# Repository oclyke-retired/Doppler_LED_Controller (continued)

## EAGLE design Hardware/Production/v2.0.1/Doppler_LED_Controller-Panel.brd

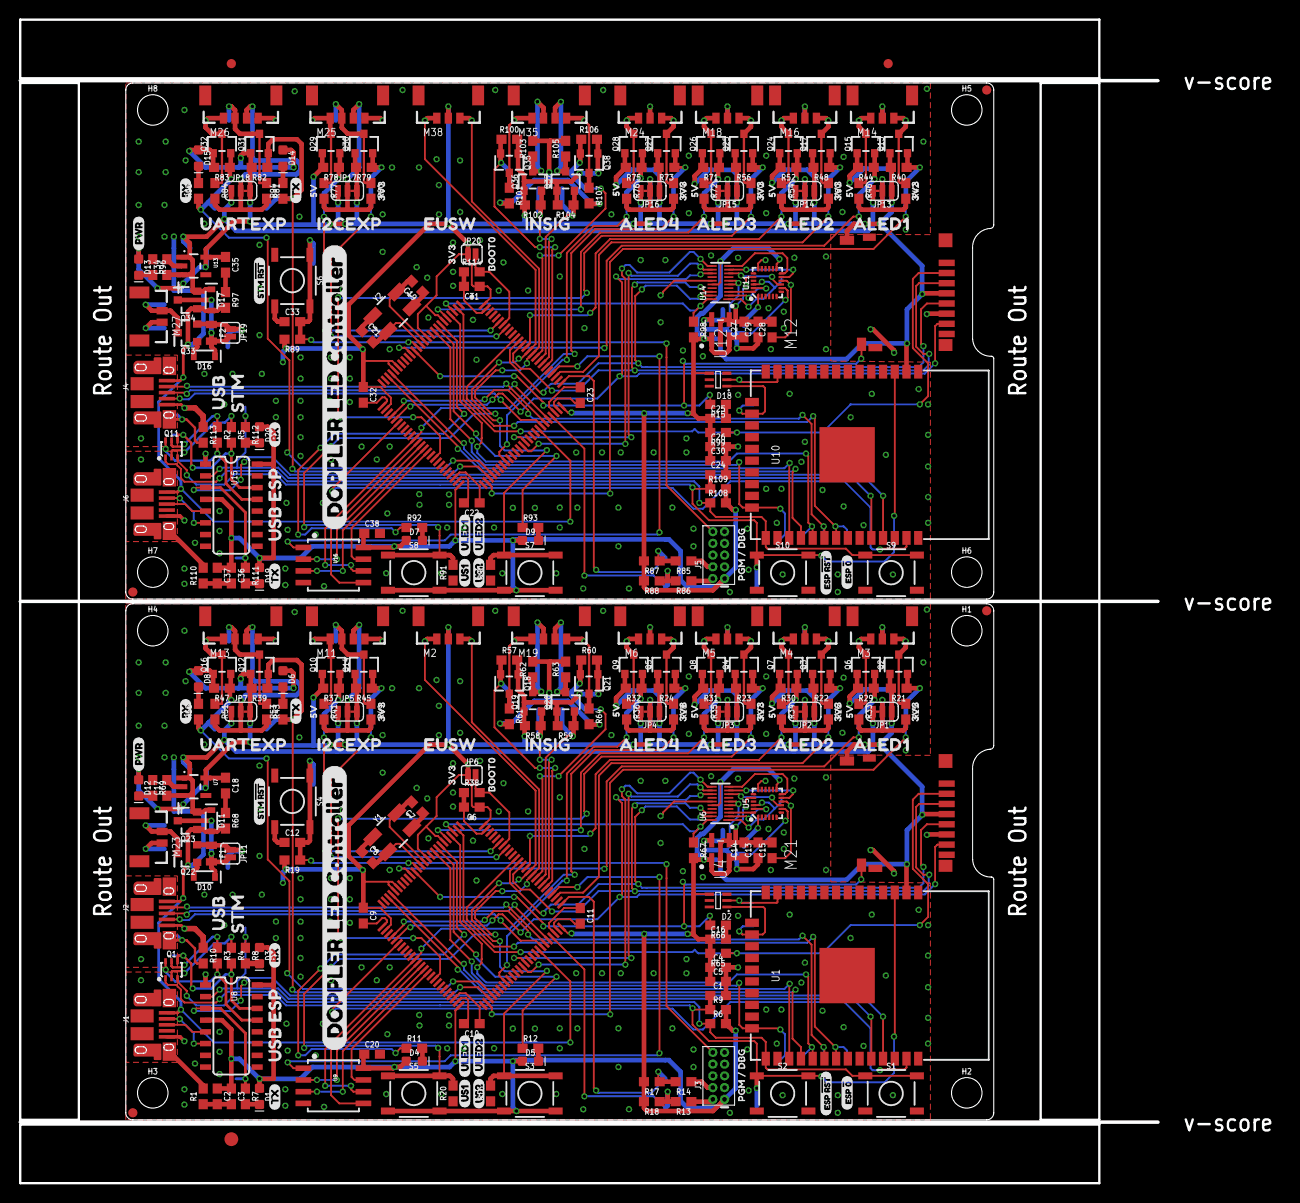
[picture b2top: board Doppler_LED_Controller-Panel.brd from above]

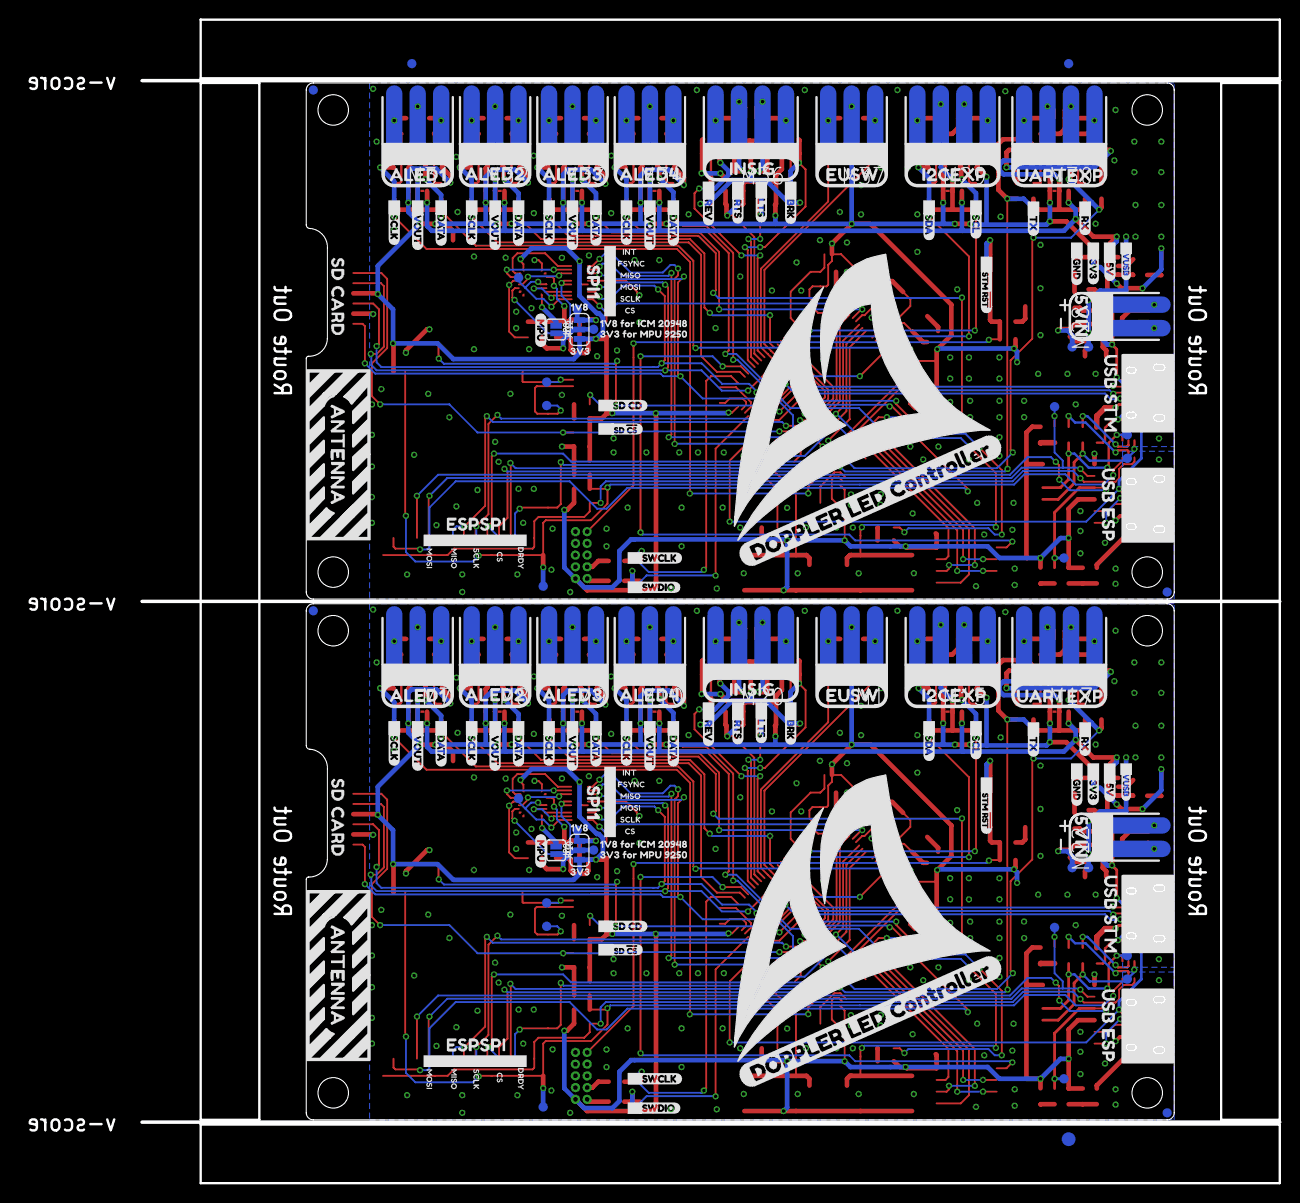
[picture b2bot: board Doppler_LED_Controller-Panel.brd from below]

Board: 2 copper layers, 123.2 x 126.0 mm, 628 parts (257 on the bottom side), 226 nets.

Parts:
C1, C3, C4, C6, C12, C13, C14, C15, C16, C20, C24, C25, C26, C27, C28, C29, C31, C33, C36, C38: 0.1uF; 0603
C2, C10, C11, C17, C18, C22, C23, C34, C35, C37: 2.2uF; 0603
C5, C9, C30, C32: 10uF; 0603
C7, C8, C19, C21: 18pF; 0603
D1, D19: ESPTX-GREEN; LED-0603
D2, D18: ESP_STAT; APA102_2020_LONG
D3, D20: ESPRX-YELLOW; LED-0603
D4, D7: ULED1-BLUE; LED-0603
D5, D9: ULED2-WHITE; LED-0603
D6, D14: U7TX-GREEN; LED-0603
D8, D15: U7RX-YELLOW; LED-0603
D10, D16: 5.6V; SOD-323
D11, D17: 3A/10V/280mV; SOD-323
D12, D13: PWR-RED; LED-0603
E$1, E$2, E$3, E$4: FIDUCIAL-1X2
E$5, E$6: FIDUCIAL-1.5X3
F1, F2: PPTC_6V500MA; 0805
FD1, FD2, FD3, FD4, FD5, FD6, FD7, FD8: FIDUCIAL1X2; FIDUCIAL-1X2
H1, H2, H3, H4, H5, H6, H7, H8: STAND-OFF
J1, J2, J4, J6: USB-MICROB-PTH-MILL
J3, J5: CORTEX_DEBUG_PTH; 2X5-PTH-1.27MM
JP1, JP13: ALED1_VOUT_SEL; SMT-JUMPER_3_1-NC_TRACE_SILK
JP2, JP14: ALED2_VOUT_SEL; SMT-JUMPER_3_1-NC_TRACE_SILK
JP3, JP15: ALED3_VOUT_SEL; SMT-JUMPER_3_1-NC_TRACE_SILK
JP4, JP16: ALED4_VOUT_SEL; SMT-JUMPER_3_1-NC_TRACE_SILK
JP5, JP7, JP17, JP18: I2C1_VOUT_SEL; SMT-JUMPER_3_1-NC_TRACE_SILK
JP6, JP20: JUMPER-SMT_2_NO_SILK; SMT-JUMPER_2_NO_SILK
JP8, JP9: IMU_VSEL; SMT-JUMPER_3_1-NC_TRACE_SILK
JP10, JP12: MPU9250; SMT-JUMPER_2_NO_SILK
JP11, JP19: DEFUSE; SMT-JUMPER_2_NO_SILK
M1, M37: EXT_SWTCH; 1X03_SMD_0.1IN
M2, M38: EXT_SWTCH; 3_PIN_LOCK
M3, M14: ALED1_LOCK; 3_PIN_LOCK
M4, M16: ALED2_LOCK; 3_PIN_LOCK
M5, M18: ALED3_LOCK; 3_PIN_LOCK
M6, M24: ALED4_LOCK; 3_PIN_LOCK
M7, M31: ALED1_SMD; 1X03_SMD_0.1IN
M8, M32: ALED2_SMD; 1X03_SMD_0.1IN
M9, M33: ALED3_SMD; 1X03_SMD_0.1IN
M10, M34: ALED4_SMD; 1X03_SMD_0.1IN
M11, M25: I2C1_LOCK; 4_PIN_LOCK
M12, M21: SD; SD_AMPHENOL_PUSH_PULL
M13, M26: U7_LOCK; 4_PIN_LOCK
M15, M29: I2C1_SMD; 1X04_SMD_0.1IN
M17, M30: U7_SMD; 1X04_SMD_0.1IN
M19, M35: SIG_IN_LOCK; 4_PIN_LOCK
M20, M36: SIG_IN_SMD; 1X04_SMD_0.1IN
M22, M28: 1X02_SMD_0.1IN
M23, M27: 2_PIN_LOCK
Q1, Q11: SC70-6
Q2, Q3, Q4, Q5, Q6, Q7, Q8, Q9, Q10, Q12, Q13, Q14, Q15, Q16, Q17, Q18, Q19, Q20, Q21, Q24, Q25, Q26, Q27, Q28, Q29, Q30, Q31, Q32, Q35, Q36, Q37, Q38: SOT23-3
Q22, Q23, Q33, Q34: 4.3A/20V/54mΩ; SOT23-3
R1, R10, R110, R113: DNP; 0603
R2, R3, R4, R5, R6, R9, R15, R16, R17, R18, R19, R20, R21, R22, R23, R24, R25, R26, R27, R28, R29, R30, R31, R32, R33, R34, R35, R36, R38, R39, R40, R42, R43, R44, R46, R47, R48, R50, R51, R52, R54, R56, R57, R58, R59, R60, R61, R62, R63, R64, R65, R66, R67, R68, R70, R71, R72, R73, R74, R75, R76, R81, R82, R83, R84, R87, R88, R89, R90, R91, R97, R98, R99, R100, R101, R102, R103, R104, R105, R106, R107, R108, R109, R114: 10k; 0603
R7, R8, R11, R12, R53, R55, R69, R92, R93, R94, R95, R96, R111, R112: 1k; 0603
R13, R14, R85, R86: 20; 0603
R37, R41, R45, R49, R77, R78, R79, R80: 2.2k; 0603
S1, S2, S3, S7, S9, S10: US2; TACTILE_SWITCH_SMD_5.2MM
S4, S6: STM_!RST; TACTILE_SWITCH_SMD_5.2MM
S5, S8: US1; TACTILE_SWITCH_SMD_5.2MM
TP1, TP104: EDRDY; PAD.03X.04
TP2, TP3: ERX0; PAD.03X.04
TP4, TP14: ETX0; PAD.03X.04
TP5, TP15: E!RTS; PAD.03X.04
TP6, TP16: E!DTR; PAD.03X.04
TP7, TP19: EMOSI; PAD.03X.04
TP8, TP26: EMISO; PAD.03X.04
TP9, TP27: ESCLK; PAD.03X.04
TP10, TP28: ECS; PAD.03X.04
TP11, TP32: ESSI; PAD.03X.04
TP12, TP33: ESSCK; PAD.03X.04
TP13, TP46: E!RST; PAD.03X.04
TP17, TP63: VDDIO; PAD.03X.04
TP18, TP73: 1V8; PAD.03X.04
TP20, TP55: S1Si; PAD.03X.04
TP21, TP56: S1SO; PAD.03X.04
TP22, TP59: S1SCLk; PAD.03X.04
TP23, TP60: CSSD; PAD.03X.04
TP24, TP61: CSIMU; PAD.03X.04
TP25, TP64: SDCD; PAD.03X.04
TP29, TP65: CSIMUIO; PAD.03X.04
TP30, TP66: IMUINT; PAD.03X.04
TP31, TP67: IMUFS; PAD.03X.04
TP34, TP81: AL1D; PAD.03X.04
TP35, TP84: AL2D; PAD.03X.04
TP36, TP87: AL3D; PAD.03X.04
TP37, TP90: AL4D; PAD.03X.04
TP38, TP82: AL1V; PAD.03X.04
TP39, TP85: AL2V; PAD.03X.04
TP40, TP88: AL3V; PAD.03X.04
TP41, TP91: AL4V; PAD.03X.04
TP42, TP83: AL1C; PAD.03X.04
TP43, TP86: AL2C; PAD.03X.04
TP44, TP89: AL3C; PAD.03X.04
TP45, TP92: AL4C; PAD.03X.04
TP47, TP74: VRPP; PAD.03X.04
TP48, TP75: VOVP; PAD.03X.04
TP49, TP76: VUSB; PAD.03X.04
TP50, TP77: 5V; PAD.03X.04
TP51, TP79: 3V3; PAD.03X.04
TP52, TP80: GND; PAD.03X.04
TP53, TP97: IIC1SDA; PAD.03X.04
TP54, TP98: IIC1SCL; PAD.03X.04
TP57, TP99: U7TX; PAD.03X.04
TP58, TP100: U7RX; PAD.03X.04
TP62, TP101: STMR; PAD.03X.04
TP68, TP102: SWCLK; PAD.03X.04
TP69, TP93: BRK; PAD.03X.04
TP70, TP94: LTS; PAD.03X.04
TP71, TP95: RTS; PAD.03X.04
TP72, TP96: REV; PAD.03X.04
TP78, TP103: SWDIO; PAD.03X.04
U1, U10: ESP-WROOM-32
U2, U3: LQFP-100
U4, U12: 1.8V; DDC5
U5, U11: 9DoF IMU; QFN24-3X3
U6, U14: TXB0108DQSR; UFDFN-20
U7, U13: 3.3V; SOT23-5
U8, U15: CH340C; SO016
U9, U16: W25Q32FVSS; SOIC-8
U$1, U$70, U$74, U$168: ALED10
U$2, U$75, U$101, U$169: ALED21
U$3, U$102: ALED43
U$4, U$76, U$103, U$170: ALED33
U$5, U$78, U$104, U$172: INSIG4
U$6, U$79, U$105, U$173: UARTEXP7
U$7, U$80, U$106, U$174: I2CEXP6
U$8, U$81, U$107, U$175: EUSW5
U$9, U$10, U$11, U$12, U$108, U$109, U$110, U$111: SCLK1
U$13, U$14, U$15, U$16, U$112, U$113, U$114, U$115: VOUT2
U$17, U$18, U$19, U$20, U$116, U$117, U$118, U$119: DATA0
U$21, U$120: RTS4
U$22, U$121: LTS3
U$23, U$122: BRK5
U$24, U$123: REV6
U$25, U$124: SCL8
U$26, U$125: SDA7
U$27, U$63, U$66, U$126, U$158, U$161: TX9
U$28, U$64, U$67, U$127, U$159, U$162: RX10
U$29, U$128: 5VIN8
U$30, U$186: VUSB15
U$31, U$187: 5V14
U$32, U$188: 3V313
U$33, U$189: GND12
U$34, U$129: SWCLK16
U$35, U$130: SWDIO15
U$36, U$48, U$131, U$143: SCLK20
U$37, U$49, U$132, U$144: CS21
U$38, U$47, U$133, U$142: MISO18
U$39, U$46, U$134, U$141: MOSI17
U$40, U$135: DRDY19
U$41, U$136: ESPSPI9
U$42, U$137: ANTENNA10
U$43, U$138: SD_CARD11
U$44, U$71, U$139, U$165: USB_ESP12
U$45, U$140: USB_STM13
U$50, U$145: FSYNC23
U$51, U$146: INT22
U$52, U$147: STM_#RST26
U$53, U$148: SD_#CS24
U$54, U$149: SD_CD27
U$55, U$68, U$150, U$163: DOPPLER_LED_CONTROLLER0
U$56, U$151: ULED23
U$57, U$152: ULED12
U$58, U$153: US10
U$59, U$154: US21
U$60, U$155: ESP_#RST5
U$61, U$156: ESP_#06
U$62, U$157: PGM_#_DBG7
U$65, U$160: PWR8
U$69, U$164: STM_#RST24
U$72, U$82, U$83, U$84, U$85, U$86, U$166, U$176, U$177, U$178, U$179, U$180: 3V310
U$73, U$167: BOOT09
U$77, U$171: ALED42
U$87, U$88, U$89, U$90, U$91, U$181, U$182, U$183, U$184, U$185: 5V11
U$92, U$190: SPI116
U$93, U$191: 3V39
U$94, U$192: 1V817
U$95, U$193: 1V8_FOR_ICM_2094818
U$96, U$194: 3V3_FOR_MPU_925019
U$97, U$195: MPU20
U$98, U$196: REV_NUM
U$99, U$197: USB0
U$100, U$198: STM1
Y1, Y2: 24MHz; CRYSTAL-SMD-5X3.2-4PAD

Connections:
1.8V: JP9.3, TP18.P$1, U4.5
1.8V1: JP8.3, TP73.P$1, U12.5
3.3V: C2.1, C3.1, C4.1, C5.1, C6.1, C9.1, C14.1, C16.1, C18.1, C20.1, D1.A, D2.4VCC, D3.A, D4.A, D5.A, D6.A, D8.A, D12.A, J3.1, JP1.1, JP2.1, JP3.1, JP4.1, JP5.3, JP6.1, JP7.3, JP9.1, M1.P$2, M2.P$2, M21.CD_SW2, M21.P$4, Q2.1, Q3.1, Q4.1, Q5.1, Q6.1, Q7.1, Q8.1, Q9.1, Q10.1, Q12.1, Q14.1, Q16.1, Q18.1, Q19.1, Q20.1, Q21.1, R6.2, R9.2, R17.2, R18.2, R19.2, R21.2, R22.2, R23.2, R24.2, R29.2, R30.2, R31.2, R32.2, R37.2, R39.2, R45.2, R47.2, R57.2, R58.2, R59.2, R60.2, R65.2, R67.2, S3.3, S3.4, S5.3, S5.4, TP51.P$1, U1.2, U3.P$6, U3.P$11, U3.P$20, U3.P$21, U3.P$27, U3.P$50, U3.P$75, U3.P$100, U4.1, U4.3, U5.13, U6.16, U7.5, U8.4, U8.16, U9.8
3.3V1: C25.1, C26.1, C27.1, C30.1, C31.1, C32.1, C35.1, C36.1, C37.1, C38.1, D7.A, D9.A, D13.A, D14.A, D15.A, D18.4VCC, D19.A, D20.A, J5.1, JP8.1, JP13.1, JP14.1, JP15.1, JP16.1, JP17.3, JP18.3, JP20.1, M12.CD_SW2, M12.P$4, M37.P$2, M38.P$2, Q13.1, Q15.1, Q17.1, Q24.1, Q25.1, Q26.1, Q27.1, Q28.1, Q29.1, Q30.1, Q31.1, Q32.1, Q35.1, Q36.1, Q37.1, Q38.1, R40.2, R44.2, R48.2, R52.2, R56.2, R71.2, R73.2, R75.2, R78.2, R79.2, R82.2, R83.2, R87.2, R88.2, R89.2, R98.2, R99.2, R100.2, R102.2, R104.2, R106.2, R108.2, R109.2, S7.3, S7.4, S8.3, S8.4, TP79.P$1, U2.P$6, U2.P$11, U2.P$20, U2.P$21, U2.P$27, U2.P$50, U2.P$75, U2.P$100, U10.2, U11.13, U12.1, U12.3, U13.5, U14.16, U15.4, U15.16, U16.8
5V: C17.1, D11.C, JP1.3, JP2.3, JP3.3, JP4.3, JP5.1, JP7.1, Q23.2, TP50.P$1, U7.1, U7.3
5V1: C34.1, D17.C, JP13.3, JP14.3, JP15.3, JP16.3, JP17.1, JP18.1, Q34.2, TP77.P$1, U13.1, U13.3
ALED1_MOSI_VOUT: M3.P$1, M7.P$1, Q6.3, R33.1
ALED1_MOSI_VOUT1: M14.P$1, M31.P$1, Q15.3, R46.1
ALED1_SCLK_VOUT: M3.P$3, M7.P$3, Q2.3, R25.1
ALED1_SCLK_VOUT1: M14.P$3, M31.P$3, Q13.3, R42.1
ALED1_VOUT: JP1.2, R25.2, R33.2, TP38.P$1
ALED1_VOUT1: JP13.2, R42.2, R46.2, TP82.P$1
ALED2_MOSI_VOUT: M4.P$1, M8.P$1, Q7.3, R34.1
ALED2_MOSI_VOUT1: M16.P$1, M32.P$1, Q24.3, R54.1
ALED2_SCLK_VOUT: M4.P$3, M8.P$3, Q3.3, R26.1
ALED2_SCLK_VOUT1: M16.P$3, M32.P$3, Q17.3, R50.1
ALED2_VOUT: JP2.2, R26.2, R34.2, TP39.P$1
ALED2_VOUT1: JP14.2, R50.2, R54.2, TP85.P$1
ALED3_MOSI_VOUT: M5.P$1, M9.P$1, Q8.3, R35.1
ALED3_MOSI_VOUT1: M18.P$1, M33.P$1, Q26.3, R72.1
ALED3_SCLK_VOUT: M5.P$3, M9.P$3, Q4.3, R27.1
ALED3_SCLK_VOUT1: M18.P$3, M33.P$3, Q25.3, R70.1
ALED3_VOUT: JP3.2, R27.2, R35.2, TP40.P$1
ALED3_VOUT1: JP15.2, R70.2, R72.2, TP88.P$1
ALED4_MOSI_VOUT: M6.P$1, M10.P$1, Q9.3, R36.1
ALED4_MOSI_VOUT1: M24.P$1, M34.P$1, Q28.3, R76.1
ALED4_SCLK_VOUT: M6.P$3, M10.P$3, Q5.3, R28.1
ALED4_SCLK_VOUT1: M24.P$3, M34.P$3, Q27.3, R74.1
ALED4_VOUT: JP4.2, R28.2, R36.2, TP41.P$1
ALED4_VOUT1: JP16.2, R74.2, R76.2, TP91.P$1
BOOT0: JP6.2, R38.2, U3.P$94
BOOT1: JP20.2, R114.2, U2.P$94
BRK: Q18.2, R57.1, TP69.P$1, U3.P$81
BRK1: Q35.2, R100.1, TP93.P$1, U2.P$81
BRK_12V: M19.P$1, M20.P$1, Q18.3, R61.1
BRK_12V1: M35.P$1, M36.P$1, Q35.3, R101.1
CS_ESP: TP10.P$1, U1.29, U3.P$4
CS_ESP1: TP28.P$1, U2.P$4, U10.29
CS_IMU: R67.1, TP24.P$1, U3.P$3, U6.20
CS_IMU1: R98.1, TP61.P$1, U2.P$3, U14.20
CS_IMU_VDDIO: TP29.P$1, U5.22, U6.1
CS_IMU_VDDIO1: TP65.P$1, U11.22, U14.1
CS_SD: M21.P$2, R65.1, TP23.P$1, U3.P$2
CS_SD1: M12.P$2, R99.1, TP60.P$1, U2.P$2
ESP_0: Q1.1, R6.1, S1.1, S1.2, U1.25
ESP_1: Q11.1, R108.1, S9.1, S9.2, U10.25
ESP_!DTR: Q1.6, R3.2, TP6.P$1, U8.13
ESP_!DTR1: Q11.6, R2.2, TP16.P$1, U15.13
ESP_!RESET: C1.1, Q1.3, R9.1, S2.1, S2.2, TP13.P$1, U1.3
ESP_!RESET1: C24.1, Q11.3, R109.1, S10.1, S10.2, TP46.P$1, U10.3
ESP_!RTS: Q1.4, R4.2, TP5.P$1, U8.14
ESP_!RTS1: Q11.4, R5.2, TP15.P$1, U15.14
ESP_DRDY: TP1.P$1, U1.24, U3.P$9
ESP_DRDY1: TP104.P$1, U2.P$9, U10.24
ESP_RXI0: R8.1, TP3.P$1, U1.34, U8.2
ESP_RXI1: R112.1, TP2.P$1, U10.34, U15.2
ESP_STAT_MOSI: D2.1DIN, TP11.P$1, U1.16
ESP_STAT_MOSI1: D18.1DIN, TP32.P$1, U10.16
ESP_STAT_SCLK: D2.2CIN, TP12.P$1, U1.13
ESP_STAT_SCLK1: D18.2CIN, TP33.P$1, U10.13
ESP_TXO0: R7.1, TP4.P$1, U1.35, U8.3
ESP_TXO1: R111.1, TP14.P$1, U10.35, U15.3
ESP_USB_DM: J1.D-, U8.6
ESP_USB_DM1: J6.D-, U15.6
ESP_USB_DP: J1.D+, U8.5
ESP_USB_DP1: J6.D+, U15.5
GND: C1.2, C2.2, C3.2, C4.2, C5.2, C6.2, C7.1, C8.1, C9.2, C10.2, C11.2, C12.1, C13.2, C14.2, C15.2, C16.2, C17.2, C18.2, C20.2, D2.3GND, D10.A, J1.GND, J2.GND, J3.3, J3.5, J3.9, M3.P$2, M4.P$2, M5.P$2, M6.P$2, M7.P$2, M8.P$2, M9.P$2, M10.P$2, M11.P$4, M13.P$4, M15.P$4, M17.P$4, M21.P$6, M22.P$1, M23.P$2, Q22.1, R1.1, R10.1, R16.1, R20.1, R38.1, R61.2, R62.2, R63.2, R64.2, R66.1, R68.1, R69.1, S1.3, S1.4, S2.3, S2.4, S4.3, S4.4, TP52.P$1, U1.1, U1.15, U1.38, U1.GND, U3.P$10, U3.P$19, U3.P$26, U3.P$49, U3.P$74, U3.P$99, U4.2, U4.4, U5.18, U5.20, U6.15, U7.2, U8.1, U9.4, Y1.2, Y1.4
GND1: C19.1, C21.1, C22.2, C23.2, C24.2, C25.2, C26.2, C27.2, C28.2, C29.2, C30.2, C31.2, C32.2, C33.1, C34.2, C35.2, C36.2, C37.2, C38.2, D16.A, D18.3GND, J4.GND, J5.3, J5.5, J5.9, J6.GND, M12.P$6, M14.P$2, M16.P$2, M18.P$2, M24.P$2, M25.P$4, M26.P$4, M27.P$2, M28.P$1, M29.P$4, M30.P$4, M31.P$2, M32.P$2, M33.P$2, M34.P$2, Q33.1, R15.1, R90.1, R91.1, R96.1, R97.1, R101.2, R103.2, R105.2, R107.2, R110.1, R113.1, R114.1, S6.3, S6.4, S9.3, S9.4, S10.3, S10.4, TP80.P$1, U2.P$10, U2.P$19, U2.P$26, U2.P$49, U2.P$74, U2.P$99, U10.1, U10.15, U10.38, U10.GND, U11.18, U11.20, U12.2, U12.4, U13.2, U14.15, U15.1, U16.4, Y2.2, Y2.4
I2C1_SCL: Q10.2, R37.1, TP54.P$1, U3.P$95
I2C1_SCL1: Q29.2, R78.1, TP98.P$1, U2.P$95
I2C1_SCL_VOUT: M11.P$1, M15.P$1, Q10.3, R41.1
I2C1_SCL_VOUT1: M25.P$1, M29.P$1, Q29.3, R77.1
I2C1_SDA: Q14.2, R45.1, TP53.P$1, U3.P$93
I2C1_SDA1: Q30.2, R79.1, TP97.P$1, U2.P$93
I2C1_SDA_VOUT: M11.P$2, M15.P$2, Q14.3, R49.1
I2C1_SDA_VOUT1: M25.P$2, M29.P$2, Q30.3, R80.1
I2C1_VOUT: JP5.2, M11.P$3, M15.P$3, R41.2, R49.2
I2C1_VOUT1: JP17.2, M25.P$3, M29.P$3, R77.2, R80.2
IMU_FSYNC: TP31.P$1, U3.P$64, U6.12
IMU_FSYNC1: TP67.P$1, U2.P$64, U14.12
IMU_FSYNC_VDDIO: U5.11, U6.9
IMU_FSYNC_VDDIO1: U11.11, U14.9
IMU_INT: TP30.P$1, U3.P$63, U6.11
IMU_INT1: TP66.P$1, U2.P$63, U14.11
IMU_INT_VDDIO: U5.12, U6.10
IMU_INT_VDDIO1: U11.12, U14.10
IMU_RESV1: JP10.1, U5.1
IMU_RESV2: JP12.1, U11.1
IMU_VDDIO: C13.1, JP9.2, JP10.2, TP17.P$1, U5.8, U6.5, U6.6
IMU_VDDIO1: C29.1, JP8.2, JP12.2, TP63.P$1, U11.8, U14.5, U14.6
LTS: Q19.2, R58.1, TP70.P$1, U3.P$82
LTS1: Q36.2, R102.1, TP94.P$1, U2.P$82
LTS_12V: M19.P$2, M20.P$2, Q19.3, R62.1
LTS_12V1: M35.P$2, M36.P$2, Q36.3, R103.1
unnamed: C23.1, U2.P$73
unnamed: J2.SHIELD, J2.SHIELD2, J2.SHIELD3, J2.SHIELD4, J2.SHIELD5, J2.SHIELD6, J2.SHIELD7, J2.SHIELD8, J2.SHIELD9, J2.SHIELD10, R10.2
unnamed: C11.1, U3.P$73
unnamed: J1.SHIELD, J1.SHIELD2, J1.SHIELD3, J1.SHIELD4, J1.SHIELD5, J1.SHIELD6, J1.SHIELD7, J1.SHIELD8, J1.SHIELD9, J1.SHIELD10, R1.2
unnamed: C10.1, U3.P$48
unnamed: C22.1, U2.P$48
unnamed: Q1.5, R3.1
unnamed: Q1.2, R4.1
unnamed: Q11.5, R2.1
unnamed: Q11.2, R5.1
unnamed: C28.1, U11.10
unnamed: J5.2, R86.1
unnamed: C15.1, U5.10
unnamed: J5.4, R85.1
unnamed: D8.C, R55.2
unnamed: J3.2, R13.1
unnamed: J3.4, R14.1
unnamed: D15.C, R95.2
unnamed: D6.C, R53.2
unnamed: D1.C, R7.2
unnamed: D3.C, R8.2
unnamed: D12.C, R69.2
unnamed: D14.C, R94.2
unnamed: D13.C, R96.2
unnamed: D5.C, R12.2
unnamed: D4.C, R11.2
unnamed: D9.C, R93.2
unnamed: D7.C, R92.2
unnamed: J6.SHIELD, J6.SHIELD2, J6.SHIELD3, J6.SHIELD4, J6.SHIELD5, J6.SHIELD6, J6.SHIELD7, J6.SHIELD8, J6.SHIELD9, J6.SHIELD10, R110.2
unnamed: D19.C, R111.2
unnamed: D20.C, R112.2
unnamed: J4.SHIELD, J4.SHIELD2, J4.SHIELD3, J4.SHIELD4, J4.SHIELD5, J4.SHIELD6, J4.SHIELD7, J4.SHIELD8, J4.SHIELD9, J4.SHIELD10, R113.2
PH0: C7.2, U3.P$12, Y1.3
PH1: C8.2, U3.P$13, Y1.1
PH2: C21.2, U2.P$13, Y2.1
PH3: C19.2, U2.P$12, Y2.3
QSPI_BK1_IO0: Q9.2, R32.1, TP37.P$1, U3.P$58
QSPI_BK1_IO5: Q28.2, R75.1, TP90.P$1, U2.P$58
QSPI_BK2_IO0: U3.P$37, U9.5
QSPI_BK2_IO1: U3.P$38, U9.2
QSPI_BK2_IO2: U3.P$39, U9.3
QSPI_BK2_IO3: U3.P$40, U9.7
QSPI_BK2_IO4: U2.P$37, U16.5
QSPI_BK2_IO5: U2.P$38, U16.2
QSPI_BK2_IO6: U2.P$39, U16.3
QSPI_BK2_IO7: U2.P$40, U16.7
QSPI_BK2_NCS: U3.P$79, U9.1
QSPI_BK2_NCS1: U2.P$79, U16.1
QSPI_SCLK: Q5.2, R24.1, TP45.P$1, U3.P$36, U9.6
QSPI_SCLK1: Q27.2, R73.1, TP92.P$1, U2.P$36, U16.6
REV: Q21.2, R60.1, TP72.P$1, U3.P$84
REV1: Q38.2, R106.1, TP96.P$1, U2.P$84
REV_12V: M19.P$4, M20.P$4, Q21.3, R64.1
REV_12V1: M35.P$4, M36.P$4, Q38.3, R107.1
RTS: Q20.2, R59.1, TP71.P$1, U3.P$83
RTS1: Q37.2, R104.1, TP95.P$1, U2.P$83
RTS_12V: M19.P$3, M20.P$3, Q20.3, R63.1
RTS_12V1: M35.P$3, M36.P$3, Q37.3, R105.1
SD_CD: M21.CD_SW1, R66.2, TP25.P$1, U3.P$15
SD_CD1: M12.CD_SW1, R15.2, TP64.P$1, U2.P$15
SPI1_MISO: M21.P$7, TP21.P$1, U3.P$30, U6.13
SPI1_MISO1: M12.P$7, TP56.P$1, U2.P$30, U14.13
SPI1_MISO_VDDIO: U5.9, U6.8
SPI1_MISO_VDDIO1: U11.9, U14.8
SPI1_MOSI: M21.P$3, TP20.P$1, U3.P$88, U6.18
SPI1_MOSI1: M12.P$3, TP55.P$1, U2.P$88, U14.18
SPI1_MOSI_VDDIO: U5.24, U6.3
SPI1_MOSI_VDDIO1: U11.24, U14.3
SPI1_SCLK: M21.P$5, TP22.P$1, U3.P$89, U6.19
SPI1_SCLK1: M12.P$5, TP59.P$1, U2.P$89, U14.19
SPI1_SCLK_VDDIO: U5.23, U6.2
SPI1_SCLK_VDDIO1: U11.23, U14.2
SPI2_MOSI: Q6.2, R29.1, TP34.P$1, U3.P$16
SPI2_MOSI1: Q15.2, R44.1, TP81.P$1, U2.P$16
SPI2_SCLK: Q2.2, R21.1, TP42.P$1, U3.P$52
SPI2_SCLK1: Q13.2, R40.1, TP83.P$1, U2.P$52
SPI3_MOSI: Q7.2, R30.1, TP35.P$1, U3.P$87
SPI3_MOSI1: Q24.2, R52.1, TP84.P$1, U2.P$87
SPI3_SCLK: Q3.2, R22.1, TP43.P$1, U3.P$78
SPI3_SCLK1: Q17.2, R48.1, TP86.P$1, U2.P$78
SPI4_MOSI: Q8.2, R31.1, TP36.P$1, U3.P$5
SPI4_MOSI1: Q26.2, R71.1, TP87.P$1, U2.P$5
SPI4_SCLK: Q4.2, R23.1, TP44.P$1, U3.P$42
SPI4_SCLK1: Q25.2, R56.1, TP89.P$1, U2.P$42
SPI6_MISO: TP8.P$1, U1.31, U3.P$90
SPI6_MISO1: TP26.P$1, U2.P$90, U10.31
SPI6_MOSI: TP7.P$1, U1.37, U3.P$31
SPI6_MOSI1: TP19.P$1, U2.P$31, U10.37
SPI6_SCLK: TP9.P$1, U1.30, U3.P$29
SPI6_SCLK1: TP27.P$1, U2.P$29, U10.30
STM_!RESET: C12.2, J3.10, R19.1, S4.1, S4.2, TP62.P$1, U3.P$14
STM_!RESET1: C33.2, J5.10, R89.1, S6.1, S6.2, TP101.P$1, U2.P$14
STM_USB_DM: J2.D-, U3.P$70
STM_USB_DM1: J4.D-, U2.P$70
STM_USB_DP: J2.D+, U3.P$71
STM_USB_DP1: J4.D+, U2.P$71
SWCLK: R14.2, R17.1, TP68.P$1, U3.P$76
SWCLK1: R85.2, R87.1, TP102.P$1, U2.P$76
SWDIO: R13.2, R18.1, TP78.P$1, U3.P$72
SWDIO1: R86.2, R88.1, TP103.P$1, U2.P$72
UART4_RX: U1.28, U3.P$23
UART4_RX1: U2.P$23, U10.28
UART4_TX: U1.27, U3.P$22
UART4_TX1: U2.P$22, U10.27
ULED1: R11.1, U3.P$7
ULED2: R12.1, U3.P$8
ULED3: R93.1, U2.P$8
ULED4: R92.1, U2.P$7
US1: M1.P$3, M2.P$3, R20.2, S5.1, S5.2, U3.P$85
US2: M1.P$1, M2.P$1, R16.2, S3.1, S3.2, U3.P$86
US3: M37.P$1, M38.P$1, R90.2, S7.1, S7.2, U2.P$86
US4: M37.P$3, M38.P$3, R91.2, S8.1, S8.2, U2.P$85
USART1_RX: Q16.2, R47.1, R55.1, TP58.P$1, U3.P$54
USART1_RX1: Q32.2, R83.1, R95.1, TP100.P$1, U2.P$54
USART1_RX_VOUT: M13.P$1, M17.P$1, Q16.3, R51.1
USART1_RX_VOUT1: M26.P$1, M30.P$1, Q32.3, R84.1
USART1_TX: Q12.2, R39.1, R53.1, TP57.P$1, U3.P$53
USART1_TX1: Q31.2, R82.1, R94.1, TP99.P$1, U2.P$53
USART1_TX_VOUT: M13.P$2, M17.P$2, Q12.3, R43.1
USART1_TX_VOUT1: M26.P$2, M30.P$2, Q31.3, R81.1
USART1_VOUT: JP7.2, M13.P$3, M17.P$3, R43.2, R51.2
USART1_VOUT1: JP18.2, M26.P$3, M30.P$3, R81.2, R84.2
USB_OTG_FS_ID: J2.ID, U3.P$69
USB_OTG_FS_ID1: J4.ID, U2.P$69
VOVP: D10.C, F1.2, JP11.2, Q23.3, TP48.P$1
VOVP1: D16.C, F2.2, JP19.2, Q34.3, TP75.P$1
VRAW: M22.P$2, M23.P$3, Q22.3
VRAW1: M27.P$3, M28.P$2, Q33.3
VRPP: F1.1, JP11.1, Q22.2, TP47.P$1
VRPP1: F2.1, JP19.1, Q33.2, TP74.P$1
V_USB: D11.A, J1.VBUS, J2.VBUS, Q23.1, R68.2, TP49.P$1, U3.P$68
V_USB1: D17.A, J4.VBUS, J6.VBUS, Q34.1, R97.2, TP76.P$1, U2.P$68

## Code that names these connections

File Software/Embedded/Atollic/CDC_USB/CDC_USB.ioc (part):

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Mcu.Name=STM32F765V(G-I)Tx
Mcu.Package=LQFP100
Mcu.UserName=STM32F765VGTx
PA0/WKUP.Mode=Asynchronous
PA0/WKUP.Signal=UART4_TX
PA1.Mode=Asynchronous
PA1.Signal=UART4_RX
PA11.Mode=Device_Only
PA11.Signal=USB_OTG_FS_DM
PA12.Mode=Device_Only
PA12.Signal=USB_OTG_FS_DP
PA13.Mode=Serial_Wire
PA13.Signal=SYS_JTMS-SWDIO
PA14.Mode=Serial_Wire
PA14.Signal=SYS_JTCK-SWCLK
PA5.Mode=Full_Duplex_Master
PA5.Signal=SPI6_SCK
PA6.Mode=Full_Duplex_Master
PA6.Signal=SPI1_MISO
PA7.Mode=Full_Duplex_Master
PA7.Signal=SPI6_MOSI
PA8.Mode=Activate_SOF_FS
PA8.Signal=USB_OTG_FS_SOF
PA9.Mode=Activate_VBUS
PA9.Signal=USB_OTG_FS_VBUS
PB10.Mode=I2C
PB10.Signal=I2C2_SCL
PB11.Mode=I2C
PB11.Signal=I2C2_SDA
PB12.Mode=Asynchronous
PB12.Signal=UART5_RX
PB13.Mode=TX_Only_Simplex_Unidirect_Master
PB13.Signal=SPI2_SCK
PB14.Mode=Asynchronous
PB14.Signal=USART1_TX
PB15.Mode=Asynchronous
PB15.Signal=USART1_RX
PB2.Mode=Dual Bank
PB2.Signal=QUADSPI_CLK
PB3.Mode=Full_Duplex_Master
PB3.Signal=SPI1_SCK
PB4.Mode=Full_Duplex_Master
PB4.Signal=SPI6_MISO
PB6.Mode=Enable Chip Select for each bank
PB6.Signal=QUADSPI_BK1_NCS
PB7.Mode=I2C
PB7.Signal=I2C1_SDA
PB8.Mode=I2C
PB8.Signal=I2C1_SCL
PC0.GPIOParameters=GPIO_Label
PC0.GPIO_Label=SD_CD
PC0.Signal=GPIO_Input
PC1.Mode=TX_Only_Simplex_Unidirect_Master
PC1.Signal=SPI2_MOSI
PC10.Mode=TX_Only_Simplex_Unidirect_Master
PC10.Signal=SPI3_SCK
PC11.Mode=Enable Chip Select for each bank
PC11.Signal=QUADSPI_BK2_NCS
PC12.Mode=Asynchronous
PC12.Signal=UART5_TX
PC13.GPIOParameters=PinState,GPIO_Label
PC13.GPIO_Label=ULED1
PC13.PinState=GPIO_PIN_SET
PC13.Signal=GPIO_Output
PC14/OSC32_IN.GPIOParameters=PinState,GPIO_PuPd,GPIO_Label
PC14/OSC32_IN.GPIO_Label=ULED2
PC14/OSC32_IN.GPIO_PuPd=GPIO_NOPULL
PC14/OSC32_IN.PinState=GPIO_PIN_SET
PC14/OSC32_IN.Signal=GPIO_Output
PC15/OSC32_OUT.GPIOParameters=GPIO_Label
PC15/OSC32_OUT.GPIO_Label=ESP_DRDY
PC15/OSC32_OUT.Signal=GPIO_Input
PC6.GPIOParameters=GPIO_Label
PC6.GPIO_Label=IMU_INT
PC6.Signal=GPIO_Input
PC7.GPIOParameters=GPIO_Label
PC7.GPIO_Label=IMU_FSYNC
PC7.Signal=GPIO_Input
PD0.GPIOParameters=GPIO_Label
PD0.GPIO_Label=BRK
PD0.Signal=GPIO_Input
PD1.GPIOParameters=GPIO_Label
PD1.GPIO_Label=LTS
PD1.Signal=GPIO_Input
PD11.Mode=Dual Bank
PD11.Signal=QUADSPI_BK1_IO0
PD12.Mode=Dual Bank
PD12.Signal=QUADSPI_BK1_IO1
PD13.Mode=Dual Bank
PD13.Signal=QUADSPI_BK1_IO3
PD2.GPIOParameters=GPIO_Label
PD2.GPIO_Label=RTS
PD2.Signal=GPIO_Input
PD3.GPIOParameters=GPIO_Label
PD3.GPIO_Label=REV
PD3.Signal=GPIO_Input
PD4.GPIOParameters=GPIO_Label
PD4.GPIO_Label=US1
PD4.Signal=GPIO_Input
PD5.GPIOParameters=GPIO_Label
PD5.GPIO_Label=US2
PD5.Signal=GPIO_Input
PD6.Mode=TX_Only_Simplex_Unidirect_Master
PD6.Signal=SPI3_MOSI
PD7.Mode=Full_Duplex_Master
PD7.Signal=SPI1_MOSI
PE0.Mode=Asynchronous
PE0.Signal=UART8_RX
PE1.Mode=Asynchronous
PE1.Signal=UART8_TX
PE10.Mode=Dual Bank
PE10.Signal=QUADSPI_BK2_IO3
PE12.Mode=TX_Only_Simplex_Unidirect_Master
PE12.Signal=SPI4_SCK
PE2.Mode=Dual Bank
PE2.Signal=QUADSPI_BK1_IO2
PE3.GPIOParameters=GPIO_Speed,PinState,GPIO_Label
PE3.GPIO_Label=CS_SD
PE3.GPIO_Speed=GPIO_SPEED_FREQ_VERY_HIGH
PE3.PinState=GPIO_PIN_SET
PE3.Signal=GPIO_Output
PE4.GPIOParameters=GPIO_Speed,PinState,GPIO_PuPd,GPIO_Label
PE4.GPIO_Label=CS_IMU
PE4.GPIO_PuPd=GPIO_NOPULL
PE4.GPIO_Speed=GPIO_SPEED_FREQ_VERY_HIGH
PE4.PinState=GPIO_PIN_SET
PE4.Signal=GPIO_Output
PE5.GPIOParameters=GPIO_Speed,PinState,GPIO_PuPd,GPIO_Label
PE5.GPIO_Label=CS_ESP
PE5.GPIO_PuPd=GPIO_NOPULL
PE5.GPIO_Speed=GPIO_SPEED_FREQ_VERY_HIGH
PE5.PinState=GPIO_PIN_SET
PE5.Signal=GPIO_Output
PE6.Mode=TX_Only_Simplex_Unidirect_Master
PE6.Signal=SPI4_MOSI
PE7.Mode=Dual Bank
PE7.Signal=QUADSPI_BK2_IO0
PE8.Mode=Dual Bank
PE8.Signal=QUADSPI_BK2_IO1
PE9.Mode=Dual Bank
PE9.Signal=QUADSPI_BK2_IO2
PH0/OSC_IN.Mode=HSE-External-Oscillator
PH0/OSC_IN.Signal=RCC_OSC_IN
PH1/OSC_OUT.Mode=HSE-External-Oscillator
PH1/OSC_OUT.Signal=RCC_OSC_OUT
RCC.HSE_VALUE=24000000
RCC.SYSCLKFreq_VALUE=216000000
RCC.SYSCLKSource=RCC_SYSCLKSOURCE_PLLCLK
board=custom

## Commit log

2018-11-28 Initial Commit
    In this commit all relevant files from the MT/AES project were copied into this repo.
2018-12-01 Added more resources
2018-12-01 Fixed clock and NVIC in default peripheral configuration
2018-12-16 Add SPI Flash Library and STM32F7 Quadspi port
2018-12-16 Add STM32F7 port for SPIDS
2018-12-16 Add SPIDS library
2018-12-16 Add SPIDS supporting files
2018-12-16 Add USB specification documents
2018-12-16 Add USB Device Configuration
2018-12-16 Add USB CDC example project
2018-12-16 Add DoppBoot project
2018-12-16 Add ESP Relay project
2018-12-16 Add USB MSC example project
2018-12-24 Add print header
2018-12-24 Add doppler bootloader header files
2018-12-24 Add printing ports for stm32f7
2018-12-24 Add bootloader atollic project
